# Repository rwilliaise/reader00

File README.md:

# reader00

The objective of reader00 is to read the memory off of a flash memory IC found
inside of consumer electronics. It is unknown if the memory on the chip is 1.
recoverable or 2. publishable.

## Chip details

The IC in question is an MX29GL128FHT2I-90G loaded with unknown data, presumably
audio files. It uses a 18.4mm x 14mm 56-pin TSOP casing.

To read the data off of the chip, I use an Arduino Nano socket on a
custom-designed PCB board. Onto this PCB board, I sotter the flash memory onto
before putting a programmed Arduino to read off of the flash memory.

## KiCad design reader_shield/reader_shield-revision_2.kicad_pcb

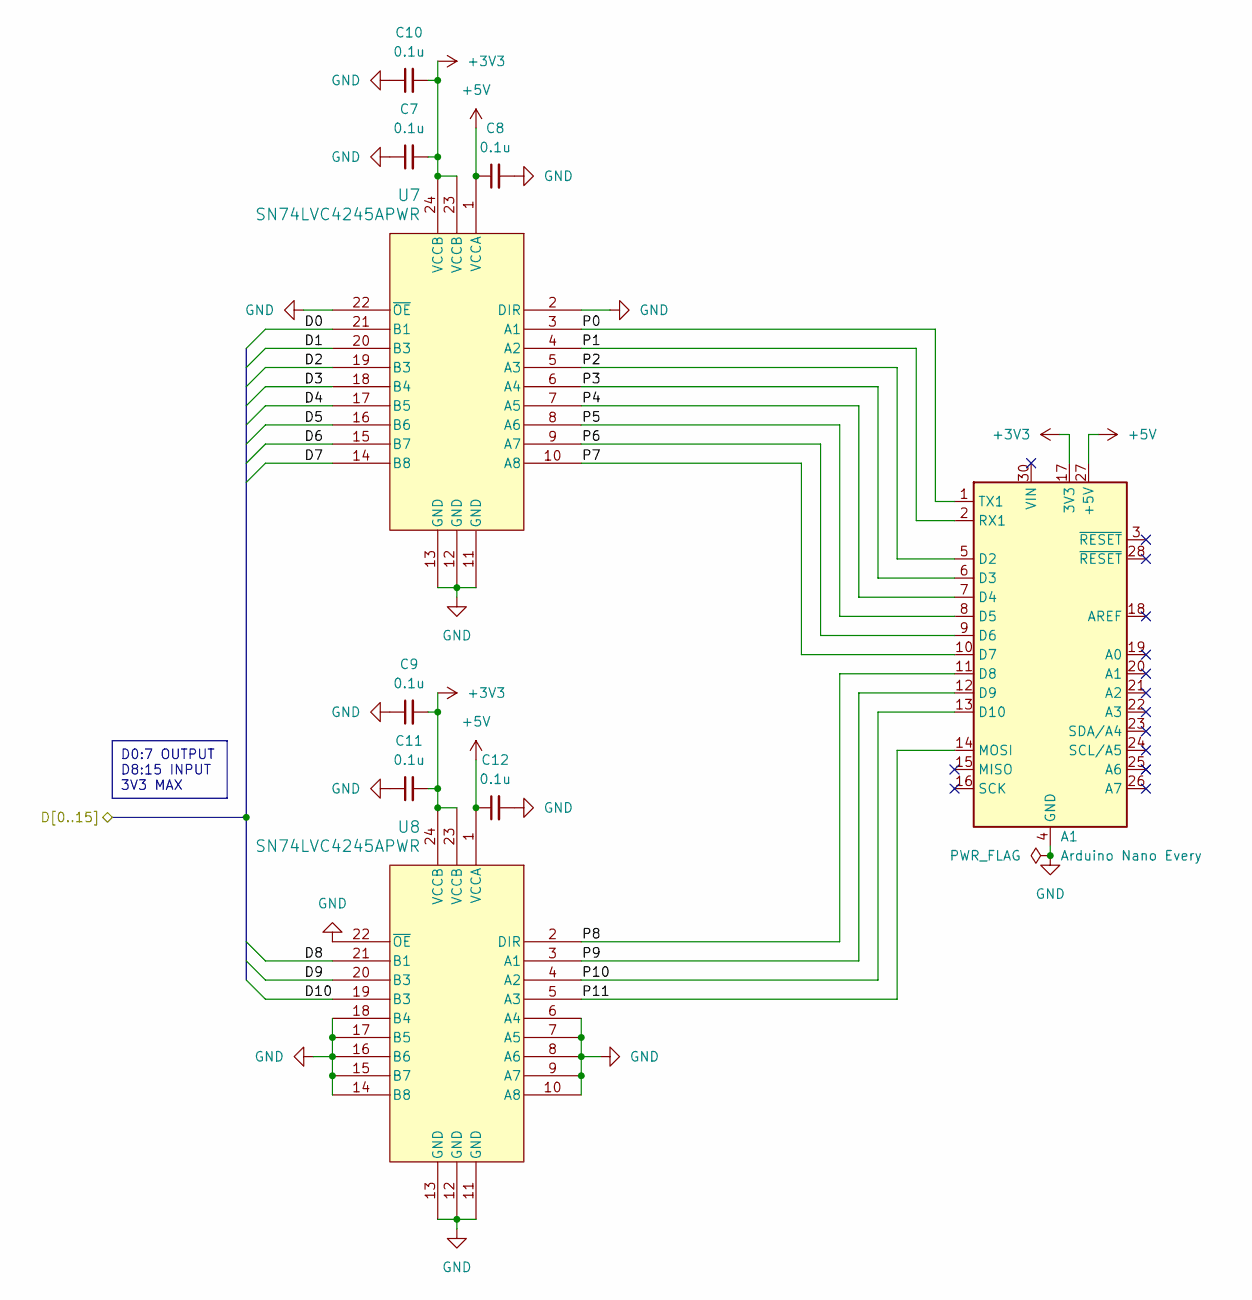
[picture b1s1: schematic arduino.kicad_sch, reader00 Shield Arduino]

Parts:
A1: Arduino Nano Every; Arduino_Nano
C7, C8, C9, C10, C11, C12: 0.1u; C_0402_1005Metric; JLCPCB Part # C1525
U7, U8: SN74LVC4245APWR; TSSOP-24_4.4x6.5mm_P0.5mm; JLCPCB Part # C7859

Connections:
+3V3: A1.17 (3V3), C7.2, C9.2, C10.2, C11.2, U7.23 (VCCB), U7.24 (VCCB), U8.23 (VCCB), U8.24 (VCCB); also elsewhere on the board
+5V: A1.27 (+5V), C8.1, C12.1, U7.1 (VCCA), U8.1 (VCCA)
/arduino/D0: U7.21 (B1); also elsewhere on the board
/arduino/D1: U7.20 (B3); also elsewhere on the board
/arduino/D2: U7.19 (B3); also elsewhere on the board
/arduino/D3: U7.18 (B4); also elsewhere on the board
/arduino/D4: U7.17 (B5); also elsewhere on the board
/arduino/D5: U7.16 (B6); also elsewhere on the board
/arduino/D6: U7.15 (B7); also elsewhere on the board
/arduino/D7: U7.14 (B8); also elsewhere on the board
/arduino/D8: U8.21 (B1); also elsewhere on the board
/arduino/D9: U8.20 (B3); also elsewhere on the board
/arduino/D10: U8.19 (B3); also elsewhere on the board
/arduino/P0: A1.1 (TX1), U7.3 (A1)
/arduino/P1: A1.2 (RX1), U7.4 (A2)
/arduino/P2: A1.5 (D2), U7.5 (A3)
/arduino/P3: A1.6 (D3), U7.6 (A4)
/arduino/P4: A1.7 (D4), U7.7 (A5)
/arduino/P5: A1.8 (D5), U7.8 (A6)
/arduino/P6: A1.9 (D6), U7.9 (A7)
/arduino/P7: A1.10 (D7), U7.10 (A8)
/arduino/P8: A1.11 (D8), U8.2 (DIR)
/arduino/P9: A1.12 (D9), U8.3 (A1)
/arduino/P10: A1.13 (D10), U8.4 (A2)
/arduino/P11: A1.14 (MOSI), U8.5 (A3)
GND: A1.4 (GND), A1.29 (GND), C7.1, C8.2, C9.1, C10.1, C11.1, C12.2, U7.2 (DIR), U7.11 (GND), U7.12 (GND), U7.13 (GND), U7.22 (~OE), U8.6 (A4), U8.7 (A5), U8.8 (A6), U8.9 (A7), U8.10 (A8), U8.11 (GND), U8.12 (GND), U8.13 (GND), U8.14 (B8), U8.15 (B7), U8.16 (B6), U8.17 (B5), U8.18 (B4), U8.22 (~OE); also elsewhere on the board

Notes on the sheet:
D0:7 OUTPUT D8:15 INPUT 3V3 MAX

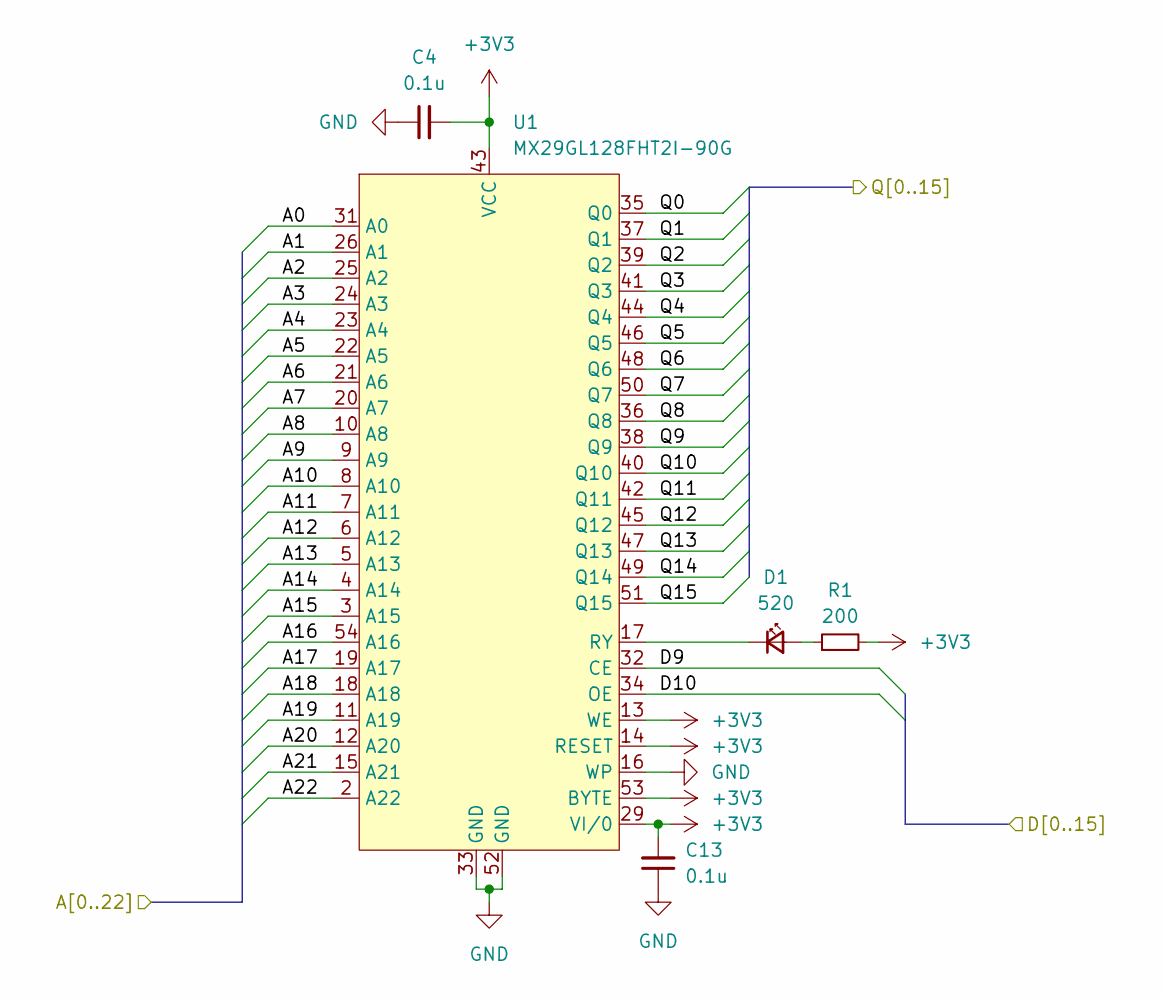
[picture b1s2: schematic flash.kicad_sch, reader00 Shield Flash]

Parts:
C4, C13: 0.1u; C_0402_1005Metric; JLCPCB Part # C1525
D1: 520; LED_0603_1608Metric; JLCPCB Part # C72043
R1: 200; R_0603_1608Metric; JLCPCB Part # C8218
U1: MX29GL128FHT2I-90G; TSOP-I-56_18.4x14mm_P0.5mm

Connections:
+3V3: C4.2, C13.2, R1.2, U1.13 (WE), U1.14 (RESET), U1.29 (VI/0), U1.43 (VCC), U1.53 (BYTE); also elsewhere on the board
/arduino/D9: U1.32 (CE); also elsewhere on the board
/arduino/D10: U1.34 (OE); also elsewhere on the board
/flash/A0: U1.31 (A0); also elsewhere on the board
/flash/A1: U1.26 (A1); also elsewhere on the board
/flash/A2: U1.25 (A2); also elsewhere on the board
/flash/A3: U1.24 (A3); also elsewhere on the board
/flash/A4: U1.23 (A4); also elsewhere on the board
/flash/A5: U1.22 (A5); also elsewhere on the board
/flash/A6: U1.21 (A6); also elsewhere on the board
/flash/A7: U1.20 (A7); also elsewhere on the board
/flash/A8: U1.10 (A8); also elsewhere on the board
/flash/A9: U1.9 (A9); also elsewhere on the board
/flash/A10: U1.8 (A10); also elsewhere on the board
/flash/A11: U1.7 (A11); also elsewhere on the board
/flash/A12: U1.6 (A12); also elsewhere on the board
/flash/A13: U1.5 (A13); also elsewhere on the board
/flash/A14: U1.4 (A14); also elsewhere on the board
/flash/A15: U1.3 (A15); also elsewhere on the board
/flash/A16: U1.54 (A16); also elsewhere on the board
/flash/A17: U1.19 (A17); also elsewhere on the board
/flash/A18: U1.18 (A18); also elsewhere on the board
/flash/A19: U1.11 (A19); also elsewhere on the board
/flash/A20: U1.12 (A20); also elsewhere on the board
/flash/A21: U1.15 (A21); also elsewhere on the board
/flash/A22: U1.2 (A22); also elsewhere on the board
/flash/Q0: U1.35 (Q0); also elsewhere on the board
/flash/Q1: U1.37 (Q1); also elsewhere on the board
/flash/Q2: U1.39 (Q2); also elsewhere on the board
/flash/Q3: U1.41 (Q3); also elsewhere on the board
/flash/Q4: U1.44 (Q4); also elsewhere on the board
/flash/Q5: U1.46 (Q5); also elsewhere on the board
/flash/Q6: U1.48 (Q6); also elsewhere on the board
/flash/Q7: U1.50 (Q7); also elsewhere on the board
/flash/Q8: U1.36 (Q8); also elsewhere on the board
/flash/Q9: U1.38 (Q9); also elsewhere on the board
/flash/Q10: U1.40 (Q10); also elsewhere on the board
/flash/Q11: U1.42 (Q11); also elsewhere on the board
/flash/Q12: U1.45 (Q12); also elsewhere on the board
/flash/Q13: U1.47 (Q13); also elsewhere on the board
/flash/Q14: U1.49 (Q14); also elsewhere on the board
/flash/Q15: U1.51 (Q15); also elsewhere on the board
GND: C4.1, C13.1, U1.16 (WP), U1.33 (GND), U1.52 (GND); also elsewhere on the board
unnamed: D1.2 (A), R1.1
unnamed: D1.1 (K), U1.17 (RY)

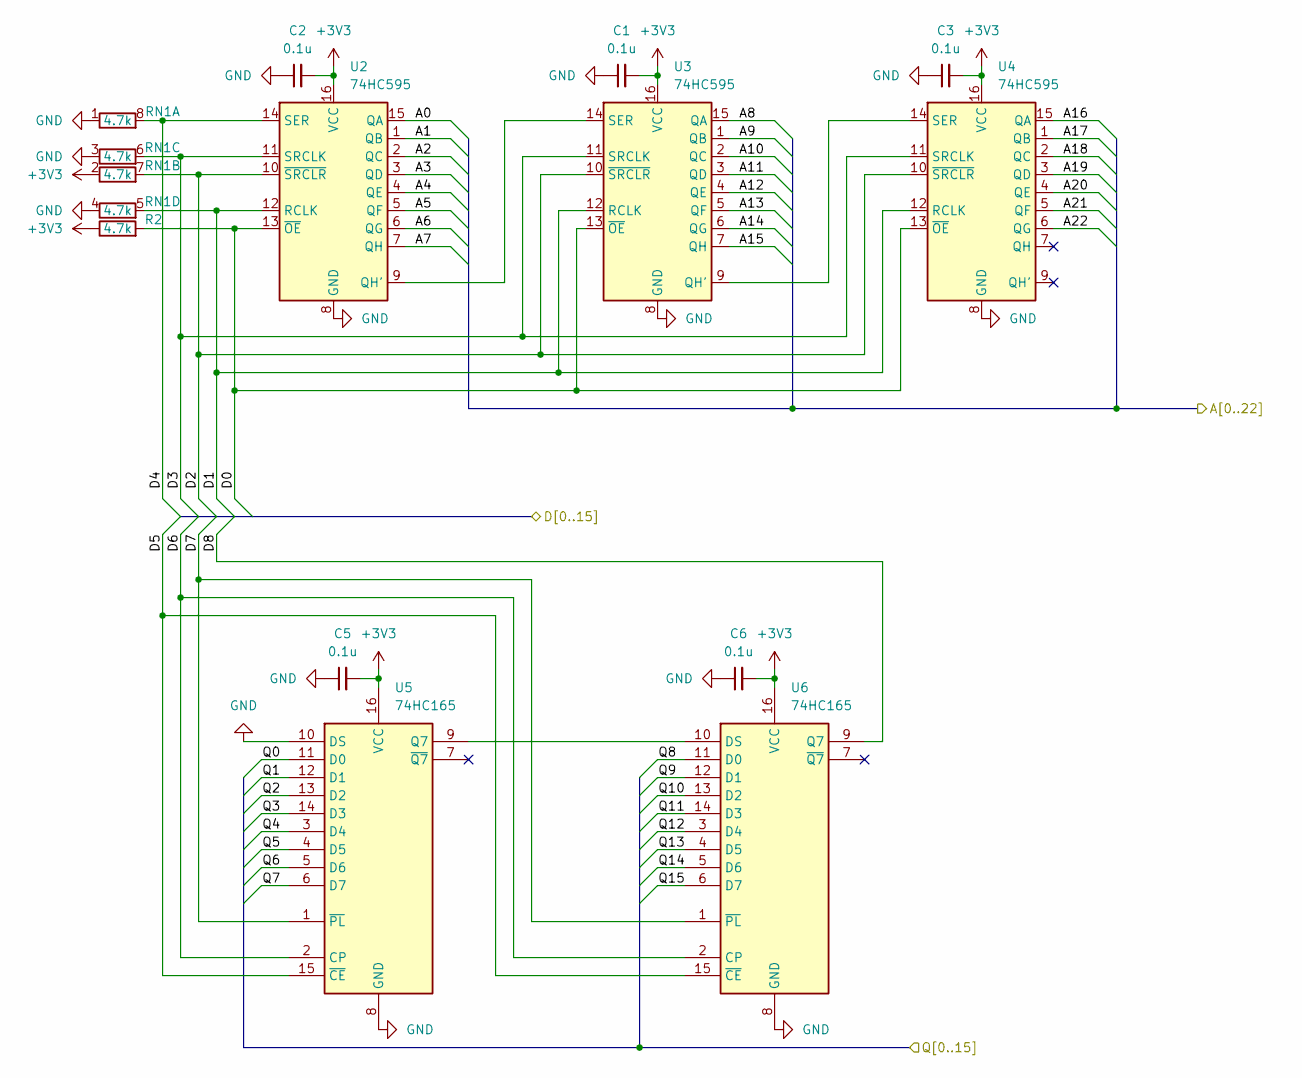
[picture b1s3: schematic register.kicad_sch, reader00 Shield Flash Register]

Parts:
C1, C2, C3, C5, C6: 0.1u; C_0402_1005Metric; JLCPCB Part # C1525
R2: 4.7k; R_0402_1005Metric; JLCPCB Part # C25900
RN1: 4.7k; R_Array_Convex_4x0603; JLCPCB Part # C1980
U2, U3, U4: 74HC595; TSSOP-16_4.4x5mm_P0.65mm; JLCPCB Part # C273642
U5, U6: 74HC165; SOIC-16_3.9x9.9mm_P1.27mm; JLCPCB Part # C5613

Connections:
+3V3: C1.2, C2.2, C3.2, C5.2, C6.2, R2.1, RN1.2 (R2.1), U2.16 (VCC), U3.16 (VCC), U4.16 (VCC), U5.16 (VCC), U6.16 (VCC); also elsewhere on the board
/arduino/D0: R2.2, U2.13 (~OE), U3.13 (~OE), U4.13 (~OE); also elsewhere on the board
/arduino/D1: RN1.5 (R4.2), U2.12 (RCLK), U3.12 (RCLK), U4.12 (RCLK); also elsewhere on the board
/arduino/D2: RN1.7 (R2.2), U2.10 (~SRCLR), U3.10 (~SRCLR), U4.10 (~SRCLR); also elsewhere on the board
/arduino/D3: RN1.6 (R3.2), U2.11 (SRCLK), U3.11 (SRCLK), U4.11 (SRCLK); also elsewhere on the board
/arduino/D4: RN1.8 (R1.2), U2.14 (SER); also elsewhere on the board
/arduino/D5: U5.15 (~CE), U6.15 (~CE); also elsewhere on the board
/arduino/D6: U5.2 (CP), U6.2 (CP); also elsewhere on the board
/arduino/D7: U5.1 (~PL), U6.1 (~PL); also elsewhere on the board
/arduino/D8: U6.9 (Q7); also elsewhere on the board
/flash/A0: U2.15 (QA); also elsewhere on the board
/flash/A1: U2.1 (QB); also elsewhere on the board
/flash/A2: U2.2 (QC); also elsewhere on the board
/flash/A3: U2.3 (QD); also elsewhere on the board
/flash/A4: U2.4 (QE); also elsewhere on the board
/flash/A5: U2.5 (QF); also elsewhere on the board
/flash/A6: U2.6 (QG); also elsewhere on the board
/flash/A7: U2.7 (QH); also elsewhere on the board
/flash/A8: U3.15 (QA); also elsewhere on the board
/flash/A9: U3.1 (QB); also elsewhere on the board
/flash/A10: U3.2 (QC); also elsewhere on the board
/flash/A11: U3.3 (QD); also elsewhere on the board
/flash/A12: U3.4 (QE); also elsewhere on the board
/flash/A13: U3.5 (QF); also elsewhere on the board
/flash/A14: U3.6 (QG); also elsewhere on the board
/flash/A15: U3.7 (QH); also elsewhere on the board
/flash/A16: U4.15 (QA); also elsewhere on the board
/flash/A17: U4.1 (QB); also elsewhere on the board
/flash/A18: U4.2 (QC); also elsewhere on the board
/flash/A19: U4.3 (QD); also elsewhere on the board
/flash/A20: U4.4 (QE); also elsewhere on the board
/flash/A21: U4.5 (QF); also elsewhere on the board
/flash/A22: U4.6 (QG); also elsewhere on the board
/flash/Q0: U5.11 (D0); also elsewhere on the board
/flash/Q1: U5.12 (D1); also elsewhere on the board
/flash/Q2: U5.13 (D2); also elsewhere on the board
/flash/Q3: U5.14 (D3); also elsewhere on the board
/flash/Q4: U5.3 (D4); also elsewhere on the board
/flash/Q5: U5.4 (D5); also elsewhere on the board
/flash/Q6: U5.5 (D6); also elsewhere on the board
/flash/Q7: U5.6 (D7); also elsewhere on the board
/flash/Q8: U6.11 (D0); also elsewhere on the board
/flash/Q9: U6.12 (D1); also elsewhere on the board
/flash/Q10: U6.13 (D2); also elsewhere on the board
/flash/Q11: U6.14 (D3); also elsewhere on the board
/flash/Q12: U6.3 (D4); also elsewhere on the board
/flash/Q13: U6.4 (D5); also elsewhere on the board
/flash/Q14: U6.5 (D6); also elsewhere on the board
/flash/Q15: U6.6 (D7); also elsewhere on the board
GND: C1.1, C2.1, C3.1, C5.1, C6.1, RN1.1 (R1.1), RN1.3 (R3.1), RN1.4 (R4.1), U2.8 (GND), U3.8 (GND), U4.8 (GND), U5.8 (GND), U5.10 (DS), U6.8 (GND); also elsewhere on the board
unnamed: U2.9 (QH'), U3.14 (SER)
unnamed: U3.9 (QH'), U4.14 (SER)
unnamed: U5.9 (Q7), U6.10 (DS)

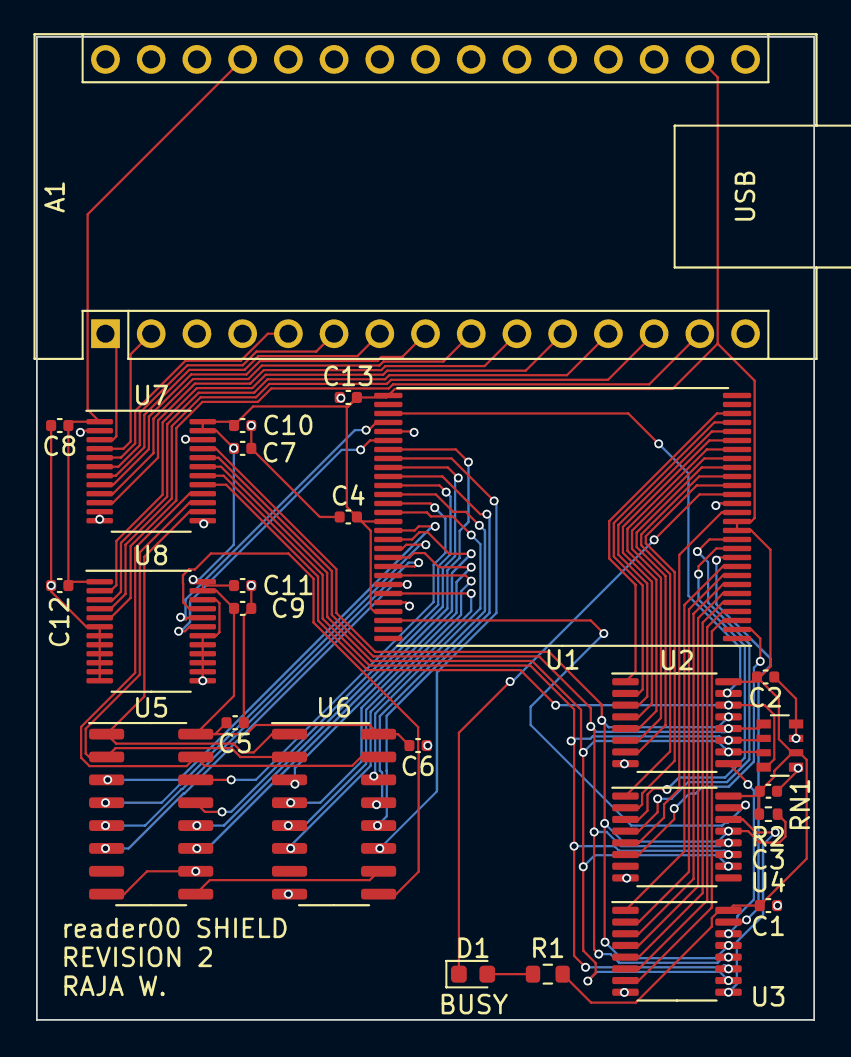
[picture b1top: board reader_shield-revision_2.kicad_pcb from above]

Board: 2 copper layers, 43.2 x 54.6 mm, 26 parts (0 on the bottom side), 70 nets.

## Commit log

2024-02-17 Remove unneeded files
2024-02-17 Describe sheets
2024-02-22 Revisions 1 and 2
